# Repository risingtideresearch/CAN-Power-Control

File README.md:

# CAN-Power-Control
CAN device for switching high-current DC loads and reading sensors and switch closures

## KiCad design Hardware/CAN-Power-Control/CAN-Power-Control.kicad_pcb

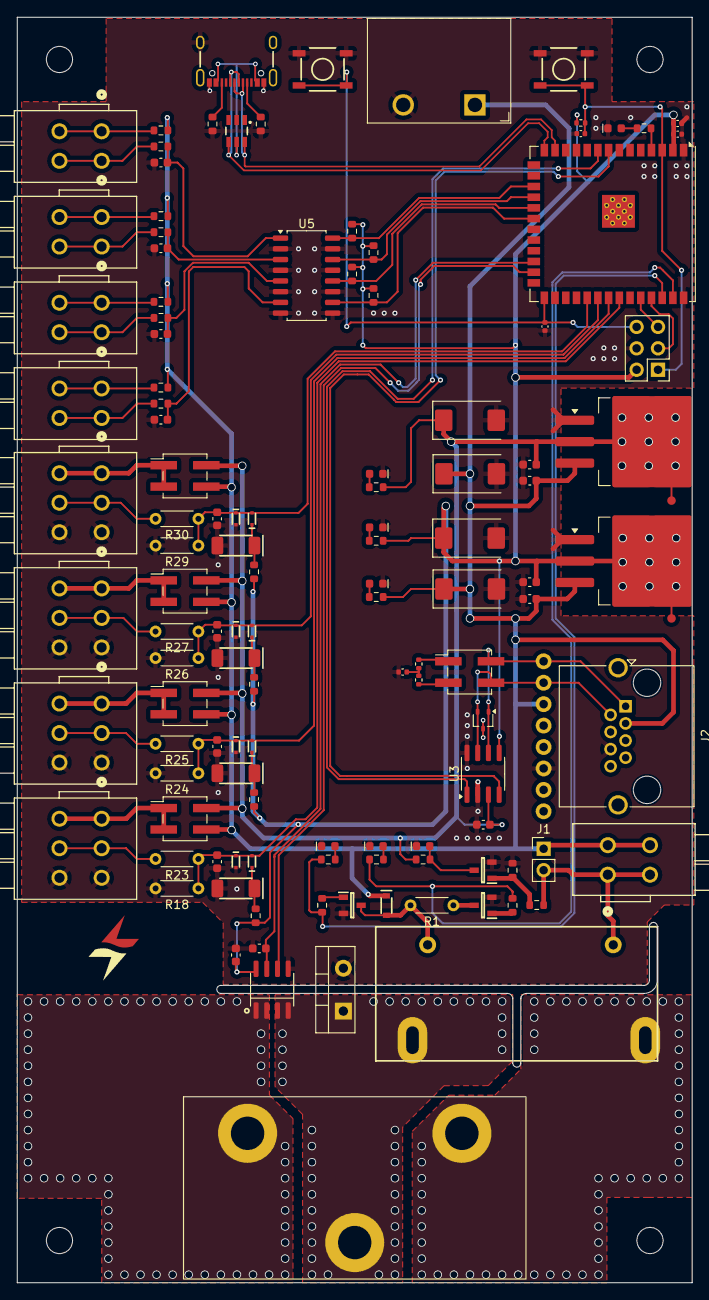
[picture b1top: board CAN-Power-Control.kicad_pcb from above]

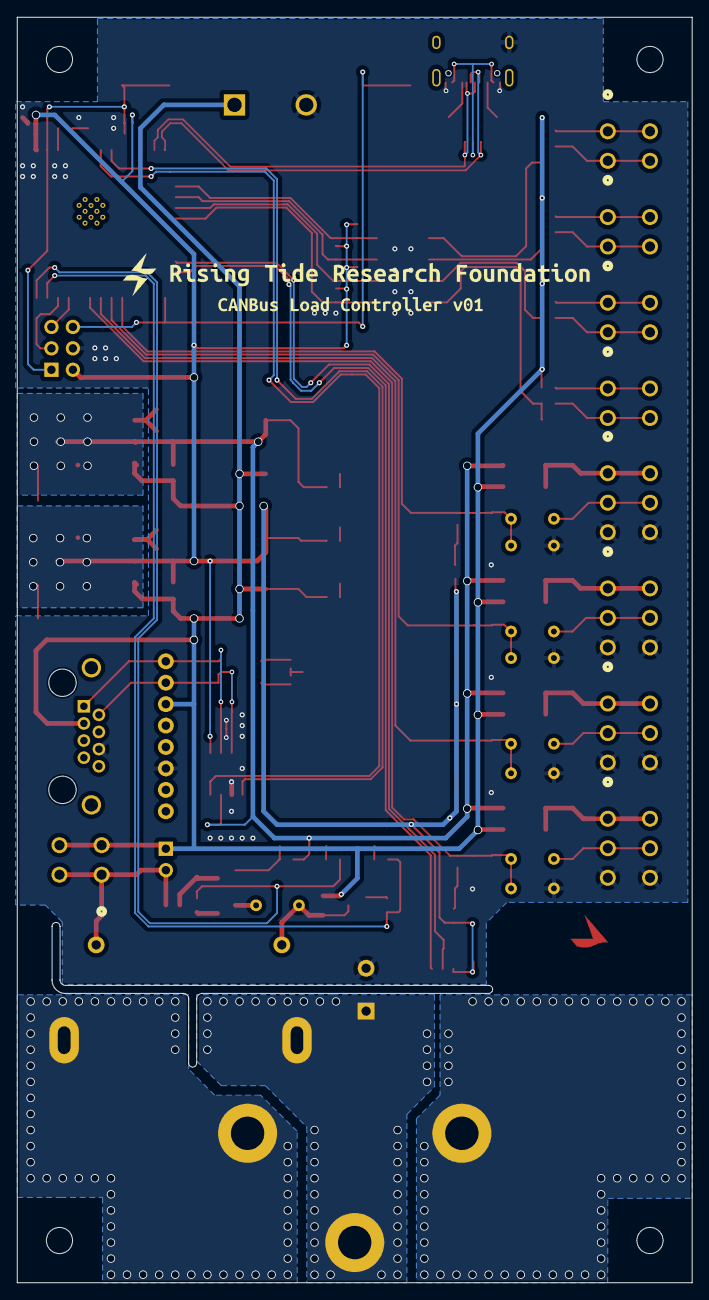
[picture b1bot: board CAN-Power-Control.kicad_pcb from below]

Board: 4 copper layers, 80.0 x 150.0 mm, 125 parts (2 on the bottom side), 73 nets.

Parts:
C1, C2, C3, C22, C23, C24, C25: 0.1uF; C_0603_1608Metric
C4, C5, C6, C7: C; C_0603_1608Metric
C8: 10uF; C_0402_1005Metric
C9: 0.1uF; C_0402_1005Metric
C10: 1.0uF; C_0402_1005Metric
C11: 4.7uF; C_0402_1005Metric
C14, C15, C16, C17: 1.0nF; C_0603_1608Metric
C18, C19, C20, C21: 10uF; CP_EIA-7343-30_AVX-N
C92: 4.7nF; C_0402_1005Metric
D1: BAT60A; SOD-323
D2: IDP30E65D1; TO-220-2_Vertical
D3, D4, D5, D20, D21, D22: Red; LED_0603_1608Metric
D6, D7, D10, D11, D13, D14, D17, D18: CDBU0520; SOD-523
D8, D9, D12, D15: Zener; SOD-128
D16: ESD2CANxx24-Q1; SOT-323_SC-70
D19: Blue; LED_0603_1608Metric
D23: DT1042-04SO; SOT23-6
J1: Conn_01x02_Pin; PinHeader_1x02_P2.54mm_Vertical
J2: 8P8C; RJ45_Amphenol_RJHSE5380
J3: Conn 01x08 Socket; 1x08
J4, J6, J7, J8, J20: WAGO 2601-1102; WAGO_1x2_2601-1102
J5, J16, J21, J23, J25: Conn_02x02_Pin; PinHeader_2x02_P2.54mm_Vertical_SMD
J9: Screw Terminal 2Pos 8.5mm Pitch; TerminalBlock_DoraboDBT10_8.5mm
J10: Conn 02x03 Odd Even; PinHeader_2x03_P2.54mm_Vertical
J11: Screw Terminal 3Pos 12.7mm Pitch; TerminalBlock_Molex_0389690003
J12: USB-C Receptacle; USB-C_16
J17, J22, J24, J26: WAGO 2601-1103; WAGO_1x3_2601-1103
K1: Power Relay AZDC007; AZDC007
Q1, Q2, Q3: FMMT625TA; SOT96P240X110-3N
R1, R18, R23, R24, R25, R26, R27, R29, R30: 1k; R_Axial_DIN0204_L3.6mm_D1.6mm_P5.08mm_Horizontal
R2, R3, R5, R7, R8, R17, R28, R35: 1k; R_0603_1608Metric
R4, R33, R34: 200; R_0603_1608Metric
R6, R9, R10, R11, R12, R13, R14, R15, R16: 330; R_0603_1608Metric
R19, R20, R21, R22: 10k; R_0603_1608Metric
R32: 10k; R_0402_1005Metric
R36: 1Meg; R_0603_1608Metric
R37, R42: 470; R_0603_1608Metric
R38, R41: 5.1k; R_0603_1608Metric
R39, R40: 60.4R; R_0402_1005Metric
SW1, SW2: SMD_5.2x5.2mm_h1.9mm; Push_SMD_5.2x5.2mm_h1.9mm
TP3, TP4: 1.0mm; TestPoint-1.0mm
U2: ACS71240LLCBTR-050U5; SOIC-8_3.9x4.9mm_P1.27mm_Power
U3: MCP2562-E-SN; SOIC-8_3.9x4.9mm_P1.27mm
U4: LM1085-3.3; TO-263-3_TabPin2
U5: TCMT4100; SOP-16_4.4x10.4mm_P1.27mm
U6: ESP32-S3-WROOM-1U-N16R2; ESP32-S3-WROOM-1U
U7: LM1085-5.0; TO-263-3_TabPin2
kibuzzard-6881B6C9: G***; kibuzzard-6881B6C9
kibuzzard-6881B704: G***; kibuzzard-6881B704

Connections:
3.3V: C1.1, C8.1, C11.1, C21.1, C25.1, J10.2, R7.1, R8.1, R17.1, R19.2, R20.2, R21.2, R22.2, R28.1, R32.2, R34.2, TP4.1, U2.8 (VCC), U3.5 (Vio), U4.2 (VO), U6.2 (VDD)
5V: C2.1, C20.1, C22.1, J16.2, J21.2, J23.2, J25.2, R6.2, R37.1, TP3.1, U3.3 (VDD), U7.2 (VO)
ACS71240 IMeas: C3.1, U2.7 (VIOUT), U6.24 (IO47)
ACS71240 ~Fault: U2.6 (~FAULT), U6.25 (IO48)
ADC0: C17.1, D17.2 (A), D18.1 (K), R29.1, R30.1, U6.31 (IO38)
ADC1: C16.1, D13.2 (A), D14.1 (K), R26.1, R27.1, U6.32 (IO39)
ADC2: C15.1, D10.2 (A), D11.1 (K), R24.1, R25.1, U6.33 (IO40)
ADC3: C14.1, D6.2 (A), D7.1 (K), R18.1, R23.1, U6.34 (IO41)
CAN RXD: U3.4 (RXD), U6.8 (IOA15)
CAN TXD: U3.1 (TXD), U6.9 (IOA16)
ESP32_EN: C10.1, J10.1, R32.1, SW1.2, U6.3 (EN)
ESP32_RXD: J10.5, U6.36 (RXD0/IO44)
ESP32_TXD: J10.3, U6.37 (TXD0/IO43)
ESP_BOOT: C9.2, J10.6, SW2.2, U6.27 (IO0)
ESP_STATUS: R42.1, U6.4 (IOA4)
GND: C1.2, C2.2, C3.2, C4.2, C5.2, C6.2, C7.2, C8.2, C9.1, C10.2, C11.2, C14.2, C15.2, C16.2, C17.2, C18.2, C19.2, C20.2, C21.2, C22.2, C23.2, C24.2, C25.2, C92.2, D2.2 (A), D3.1 (K), D4.1 (K), D5.1 (K), D7.2 (A), D8.2 (A), D9.2 (A), D11.2 (A), D12.2 (A), D14.2 (A), D15.2 (A), D16.3 (common), D18.2 (A), D19.1 (K), D20.1 (K), D21.1 (K), D22.1 (K), D23.2 (GND), J2.6, J3.6, J9.2, J10.4, J12.GND, J12.S (SHIELD), J17.3 (2_1), J22.3 (2_1), J24.3 (2_1), J26.3 (2_1), Q1.2 (E), Q2.2 (E), Q3.2 (E), R18.2, R24.2, R26.2, R29.2, R36.1, R38.1, R41.1, SW1.1, SW2.1, U2.5 (GND), U3.2 (VSS), U3.8 (STBY), U4.1 (GND), U5.2, U5.4, U5.6, U5.8, U5.9, U5.11, U5.13, U5.15, U6.1 (GND), U6.40 (GND), U7.1 (GND)
Load Monitor: D2.1 (K), J11.2, K1.4, U2.3 (IP-), U2.4 (IP-)
Load Switch: J11.3, K1.3
Load V+: J11.1, U2.1 (IP+), U2.2 (IP+)
unnamed: C4.1, R10.2, U5.1
unnamed: C5.1, R12.2, U5.3
unnamed: C6.1, R14.2, U5.5
unnamed: C7.1, R16.2, U5.7
unnamed: C92.1, R39.1, R40.1
unnamed: D1.2 (A), K1.1, Q1.3 (C), R1.2
unnamed: D3.2 (A), R4.1
unnamed: D4.2 (A), R5.1
unnamed: D5.2 (A), R6.1
unnamed: D6.1 (K), D8.1 (K), R7.2
unnamed: D9.1 (K), D10.1 (K), R8.2
unnamed: D12.1 (K), D13.1 (K), R17.2
unnamed: D15.1 (K), D17.1 (K), R28.2
unnamed: D16.1 (A1), J2.1, J3.1, J5.2, U3.6 (CANL)
unnamed: D16.2 (A2), J2.2, J3.2, J5.4, U3.7 (CANH)
unnamed: D19.2 (A), R42.2
unnamed: D20.2 (A), R33.1
unnamed: D21.2 (A), R34.1
unnamed: D22.2 (A), Q3.3 (C), R37.2
unnamed: D23.5 (VCC), J12.VBUS
unnamed: J4.1, R9.1
unnamed: J4.2 (1), R10.1
unnamed: J5.1, R40.2
unnamed: J5.3, R39.2
unnamed: J6.1, R11.1
unnamed: J6.2 (1), R12.1
unnamed: J7.1, R13.1
unnamed: J7.2 (1), R14.1
unnamed: J8.1, R15.1
unnamed: J8.2 (1), R16.1
unnamed: J12.A5 (CC1), R41.2
unnamed: J12.B5 (CC2), R38.2
unnamed: J16.1, J16.3, J17.1 (1_1)
unnamed: J17.2 (1_2), R23.2
unnamed: J21.1, J21.3, J22.1 (1_1)
unnamed: J22.2 (1_2), R25.2
unnamed: J23.1, J23.3, J24.1 (1_1)
unnamed: J24.2 (1_2), R27.2
unnamed: J25.1, J25.3, J26.1 (1_1)
unnamed: J26.2 (1_2), R30.2
unnamed: Q1.1 (B), R2.2
unnamed: Q2.1 (B), R3.2
unnamed: Q2.3 (C), R1.1
unnamed: Q3.1 (B), R35.2, R36.2
Relay Break +: C18.1, C19.1, C23.1, C24.1, D1.1 (K), J1.1, J2.3, J3.3, J9.1, J16.4, J20.2 (1), J21.4, J23.4, J25.4, R5.2, R9.2, R11.2, R13.2, R15.2, U4.3 (VI), U7.3 (VI)
Relay Break -: J1.2, J20.1, K1.2, R35.1
Relay Close: R2.1, R4.2, U6.38 (IOA2)
Relay Hold: R3.1, R33.2, U6.39 (IOA1)
Sw0: R22.1, U5.16, U6.17 (IOA9)
Sw1: R19.1, U5.14, U6.18 (IOA10)
Sw2: R21.1, U5.12, U6.19 (IOA11)
Sw3: R20.1, U5.10, U6.20 (IOA12)
USB_DN: D23.6 (I/O4), J12.A7 (D-), J12.B7 (D-), U6.13 (IOA19)
USB_DP: D23.4 (I/O3), J12.A6 (D+), J12.B6 (D+), U6.14 (IOA20)

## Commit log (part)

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2025-06-29 Initial pre-silk layout
    - v01 schematic
    - pre-silk layout
    - update library references
2025-07-14 V01 layout almost ready for prototype
    TODO:
    - Ground stitching
    - Double-check trace widths and 50A section
2025-07-24 Minor changes
    - Replace 60R resistors with closest E96 value (60.4R)
    - Minor ground trace additions
    - Silkscreen addition
